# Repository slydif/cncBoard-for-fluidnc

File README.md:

KiCad PCB for fluidnc CNC router.
- Opto-coupled inputs with hysterese (schmitt triggers)
- 16 extra outputs with i2s driven shiftregisters.
- 2 relais can be used.
- 5 axes can be used.
- Buck-converter can be attached
- SD-card support.
- Tested and working.

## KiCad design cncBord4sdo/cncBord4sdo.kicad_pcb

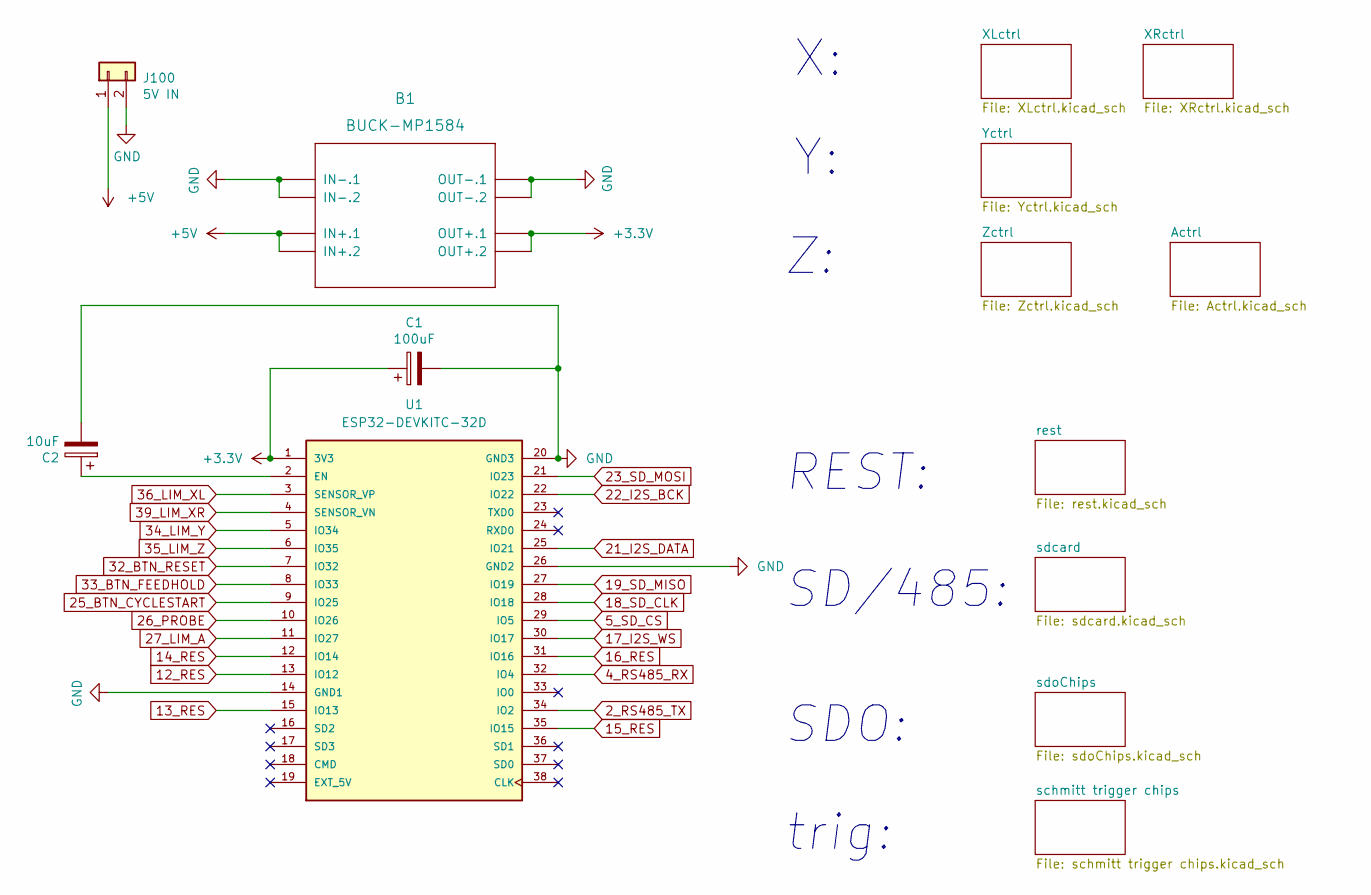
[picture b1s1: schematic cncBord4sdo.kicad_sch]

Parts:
B1: BUCK-MP1584; DC-DC-STEP-DOWN-MP1584
C1: 100uF; CP_Radial_D6.3mm_P2.50mm
C2: 10uF; CP_Radial_D6.3mm_P2.50mm
J100: 5V IN; PhoenixContact_MCV_1,5_2-G-5.08_1x02_P5.08mm_Vertical
U1: ESP32-DEVKITC-32D; MODULE_ESP32-DEVKITC-32D; PARTREV 4

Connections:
2_RS485_TX: U1.34 (IO2); also elsewhere on the board
4_RS485_RX: U1.32 (IO4); also elsewhere on the board
5_SD_CS: U1.29 (IO5); also elsewhere on the board
12_RES: U1.13 (IO12); also elsewhere on the board
13_RES: U1.15 (IO13); also elsewhere on the board
14_RES: U1.12 (IO14); also elsewhere on the board
15_RES: U1.35 (IO15); also elsewhere on the board
16_RES: U1.31 (IO16); also elsewhere on the board
17_I2S_WS: U1.30 (IO17); also elsewhere on the board
18_SD_CLK: U1.28 (IO18); also elsewhere on the board
19_SD_MISO: U1.27 (IO19); also elsewhere on the board
21_I2S_DATA: U1.25 (IO21); also elsewhere on the board
22_I2S_BCK: U1.22 (IO22); also elsewhere on the board
23_SD_MOSI: U1.21 (IO23); also elsewhere on the board
25_BTN_CYCLESTART: U1.9 (IO25); also elsewhere on the board
26_PROBE: U1.10 (IO26); also elsewhere on the board
27_LIM_A: U1.11 (IO27); also elsewhere on the board
32_BTN_RESET: U1.7 (IO32); also elsewhere on the board
33_BTN_FEEDHOLD: U1.8 (IO33); also elsewhere on the board
34_LIM_Y: U1.5 (IO34); also elsewhere on the board
35_LIM_Z: U1.6 (IO35); also elsewhere on the board
36_LIM_XL: U1.3 (SENSOR_VP); also elsewhere on the board
39_LIM_XR: U1.4 (SENSOR_VN); also elsewhere on the board
+3.3V: B1.OUT+.1, B1.OUT+.2, C1.1, U1.1 (3V3); also elsewhere on the board
+5V: B1.IN+.1, B1.IN+.2, J100.1; also elsewhere on the board
GND: B1.IN-.1, B1.IN-.2, B1.OUT-.1, B1.OUT-.2, C1.2, C2.2, J100.2, U1.14 (GND1), U1.20 (GND3), U1.26 (GND2); also elsewhere on the board
unnamed: C2.1, U1.2 (EN)

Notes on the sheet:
SDO:
trig:
SD/485:
REST:

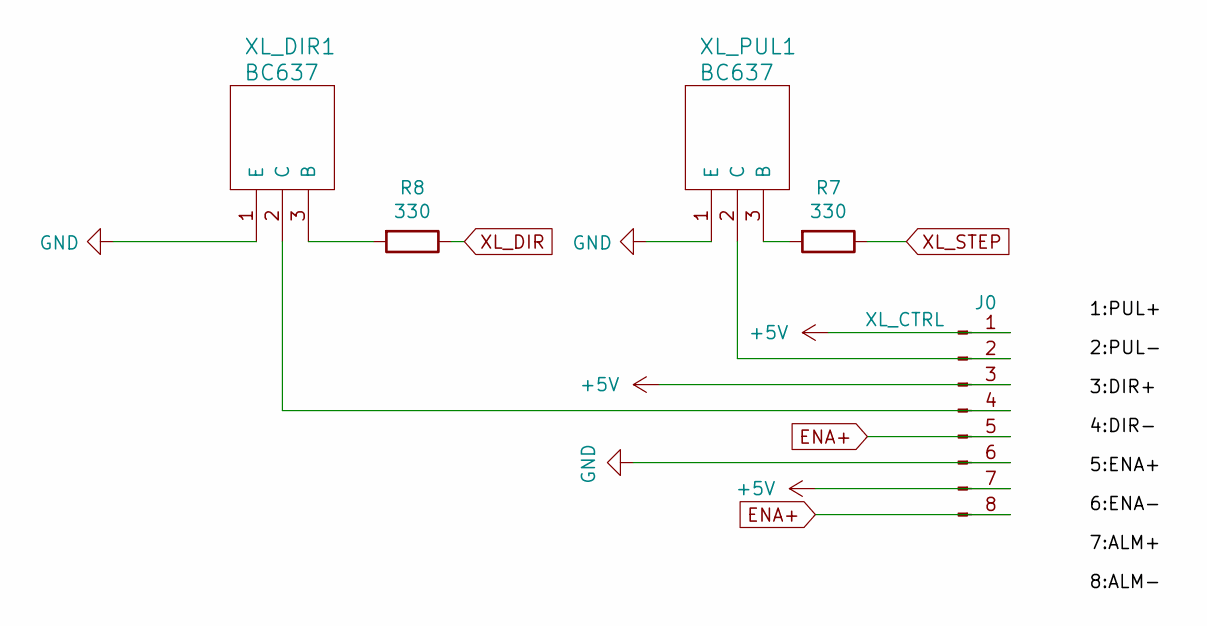
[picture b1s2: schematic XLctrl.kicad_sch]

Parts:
J0: XL_CTRL; JST_EH_B8B-EH-A_1x08_P2.50mm_Vertical
R7, R8: 330; R_1210_3225Metric_Pad1.30x2.65mm_HandSolder
XL_DIR1: BC637; TO-92_HandSolder
XL_PUL1: BC637; TO-92_HandSolder

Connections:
+5V: J0.1, J0.3, J0.7; also elsewhere on the board
ENA+: J0.5, J0.8; also elsewhere on the board
GND: J0.6, XL_DIR1.1 (E), XL_PUL1.1 (E); also elsewhere on the board
unnamed: J0.4, XL_DIR1.2 (C)
unnamed: R7.2, XL_PUL1.3 (B)
unnamed: R8.2, XL_DIR1.3 (B)
unnamed: J0.2, XL_PUL1.2 (C)
XL_DIR: R8.1; also elsewhere on the board
XL_STEP: R7.1; also elsewhere on the board

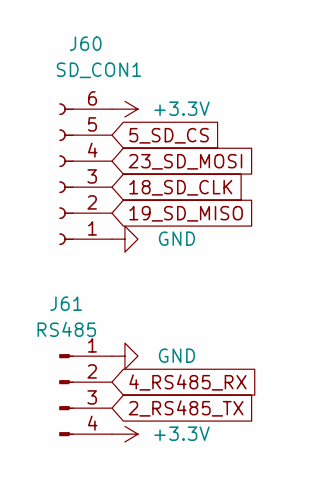
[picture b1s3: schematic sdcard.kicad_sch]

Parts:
J60: SD_CON1; PinHeader_1x06_P2.54mm_Vertical
J61: RS485; PinHeader_1x04_P2.54mm_Vertical

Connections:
2_RS485_TX: J61.3; also elsewhere on the board
4_RS485_RX: J61.2; also elsewhere on the board
5_SD_CS: J60.5; also elsewhere on the board
18_SD_CLK: J60.3; also elsewhere on the board
19_SD_MISO: J60.2; also elsewhere on the board
23_SD_MOSI: J60.4; also elsewhere on the board
+3.3V: J60.6, J61.4; also elsewhere on the board
GND: J60.1, J61.1; also elsewhere on the board

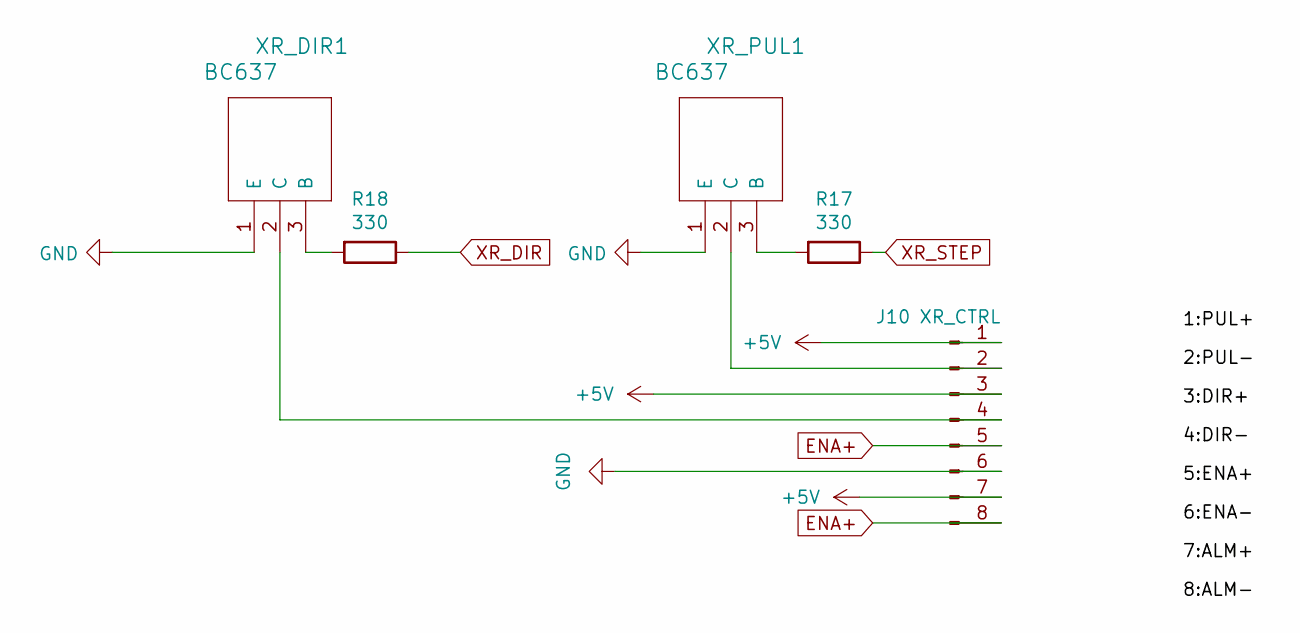
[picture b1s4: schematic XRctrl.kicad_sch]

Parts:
J10: XR_CTRL; JST_EH_B8B-EH-A_1x08_P2.50mm_Vertical
R17, R18: 330; R_1210_3225Metric_Pad1.30x2.65mm_HandSolder
XR_DIR1: BC637; TO-92_HandSolder
XR_PUL1: BC637; TO-92_HandSolder

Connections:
+5V: J10.1, J10.3, J10.7; also elsewhere on the board
ENA+: J10.5, J10.8; also elsewhere on the board
GND: J10.6, XR_DIR1.1 (E), XR_PUL1.1 (E); also elsewhere on the board
unnamed: J10.2, XR_PUL1.2 (C)
unnamed: J10.4, XR_DIR1.2 (C)
unnamed: R17.2, XR_PUL1.3 (B)
unnamed: R18.2, XR_DIR1.3 (B)
XR_DIR: R18.1; also elsewhere on the board
XR_STEP: R17.1; also elsewhere on the board

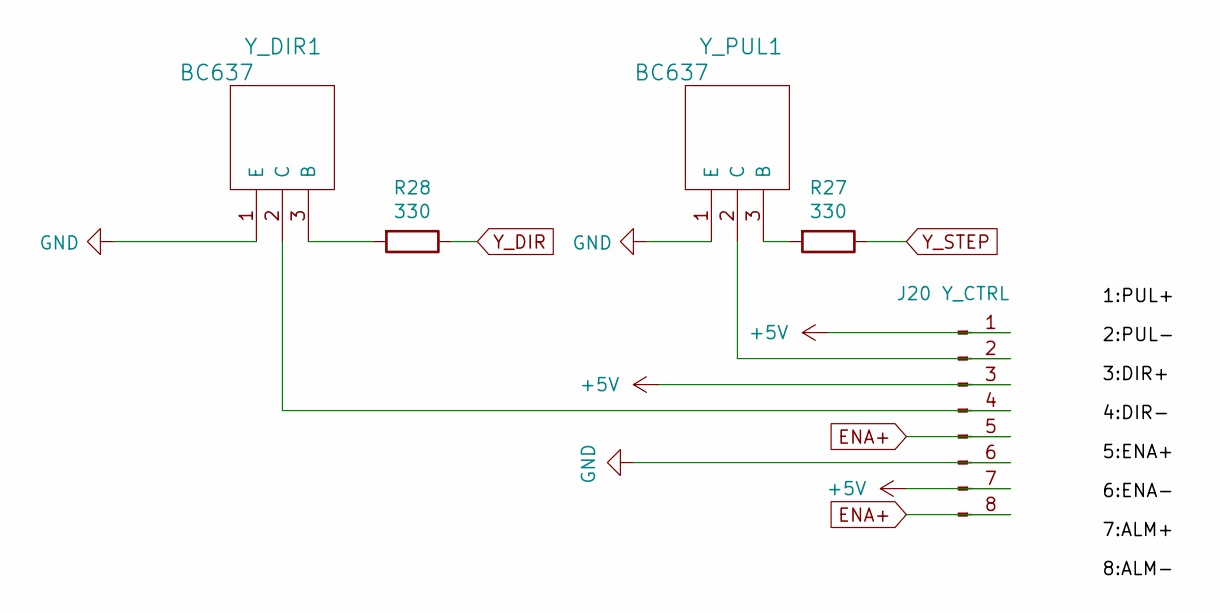
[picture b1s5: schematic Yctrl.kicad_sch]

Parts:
J20: Y_CTRL; JST_EH_B8B-EH-A_1x08_P2.50mm_Vertical
R27, R28: 330; R_1210_3225Metric_Pad1.30x2.65mm_HandSolder
Y_DIR1: BC637; TO-92_HandSolder
Y_PUL1: BC637; TO-92_HandSolder

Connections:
+5V: J20.1, J20.3, J20.7; also elsewhere on the board
ENA+: J20.5, J20.8; also elsewhere on the board
GND: J20.6, Y_DIR1.1 (E), Y_PUL1.1 (E); also elsewhere on the board
unnamed: R27.2, Y_PUL1.3 (B)
unnamed: R28.2, Y_DIR1.3 (B)
unnamed: J20.4, Y_DIR1.2 (C)
unnamed: J20.2, Y_PUL1.2 (C)
Y_DIR: R28.1; also elsewhere on the board
Y_STEP: R27.1; also elsewhere on the board

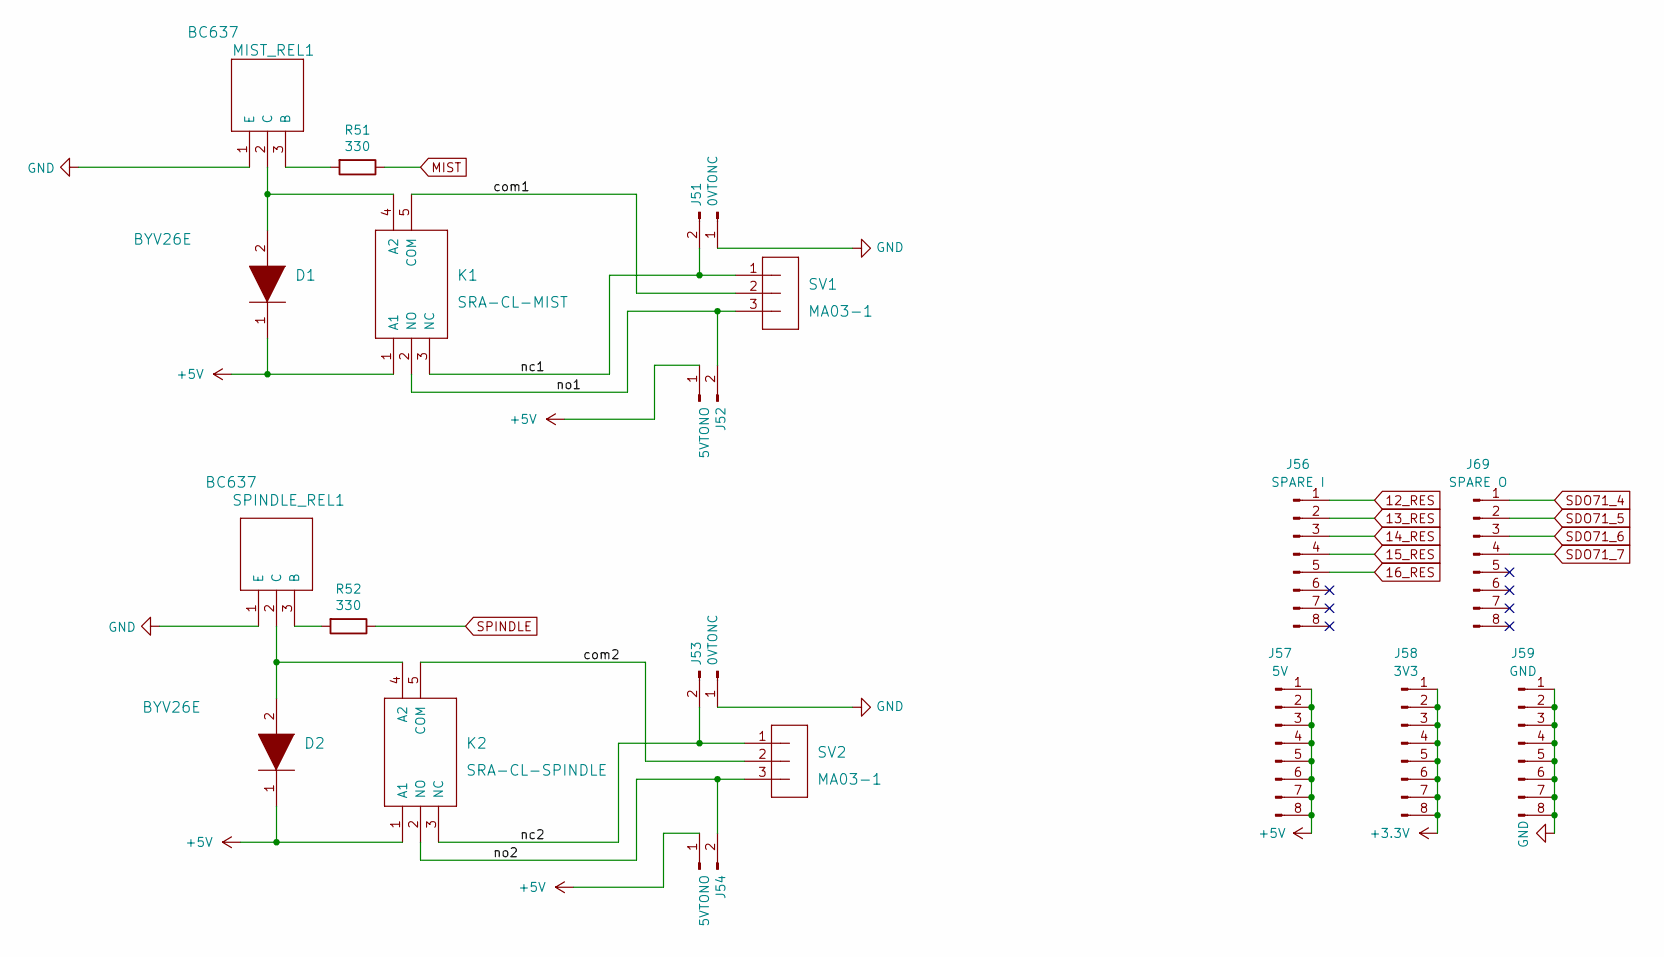
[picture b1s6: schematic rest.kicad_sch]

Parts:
D1, D2: BYV26E; D_A-405_P7.62mm_Horizontal
J51, J53: 0VTONC; PinHeader_1x02_P2.54mm_Vertical
J52, J54: 5VTONO; PinHeader_1x02_P2.54mm_Vertical
J56: SPARE I; PinHeader_1x08_P2.54mm_Vertical
J57: 5V; PinHeader_1x08_P2.54mm_Vertical
J58: 3V3; PinHeader_1x08_P2.54mm_Vertical
J59: GND; PinHeader_1x08_P2.54mm_Vertical
J69: SPARE O; PinHeader_1x08_P2.54mm_Vertical
K1: SRA-CL-MIST; SRA12VDCCL
K2: SRA-CL-SPINDLE; SRA12VDCCL
MIST_REL1: BC637; TO-92_HandSolder
R51, R52: 330; R_1210_3225Metric_Pad1.30x2.65mm_HandSolder
SPINDLE_REL1: BC637; TO-92_HandSolder
SV1, SV2: MA03-1; PhoenixContact_MCV_1,5_3-G-5.08_1x03_P5.08mm_Vertical

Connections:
12_RES: J56.1; also elsewhere on the board
13_RES: J56.2; also elsewhere on the board
14_RES: J56.3; also elsewhere on the board
15_RES: J56.4; also elsewhere on the board
16_RES: J56.5; also elsewhere on the board
+3.3V: J58.1, J58.2, J58.3, J58.4, J58.5, J58.6, J58.7, J58.8; also elsewhere on the board
+5V: D1.1 (K), D2.1 (K), J52.1, J54.1, J57.1, J57.2, J57.3, J57.4, J57.5, J57.6, J57.7, J57.8, K1.1 (A1), K2.1 (A1); also elsewhere on the board
/rest/com1: K1.5 (COM), SV1.2
/rest/com2: K2.5 (COM), SV2.2
/rest/nc1: J51.2, K1.3 (NC), SV1.1
/rest/nc2: J53.2, K2.3 (NC), SV2.1
/rest/no1: J52.2, K1.2 (NO), SV1.3
/rest/no2: J54.2, K2.2 (NO), SV2.3
GND: J51.1, J53.1, J59.1, J59.2, J59.3, J59.4, J59.5, J59.6, J59.7, J59.8, MIST_REL1.1 (E), SPINDLE_REL1.1 (E); also elsewhere on the board
MIST: R51.1; also elsewhere on the board
unnamed: D1.2 (A), K1.4 (A2), MIST_REL1.2 (C)
unnamed: D2.2 (A), K2.4 (A2), SPINDLE_REL1.2 (C)
unnamed: MIST_REL1.3 (B), R51.2
unnamed: R52.2, SPINDLE_REL1.3 (B)
SDO71_4: J69.1; also elsewhere on the board
SDO71_5: J69.2; also elsewhere on the board
SDO71_6: J69.3; also elsewhere on the board
SDO71_7: J69.4; also elsewhere on the board
SPINDLE: R52.1; also elsewhere on the board

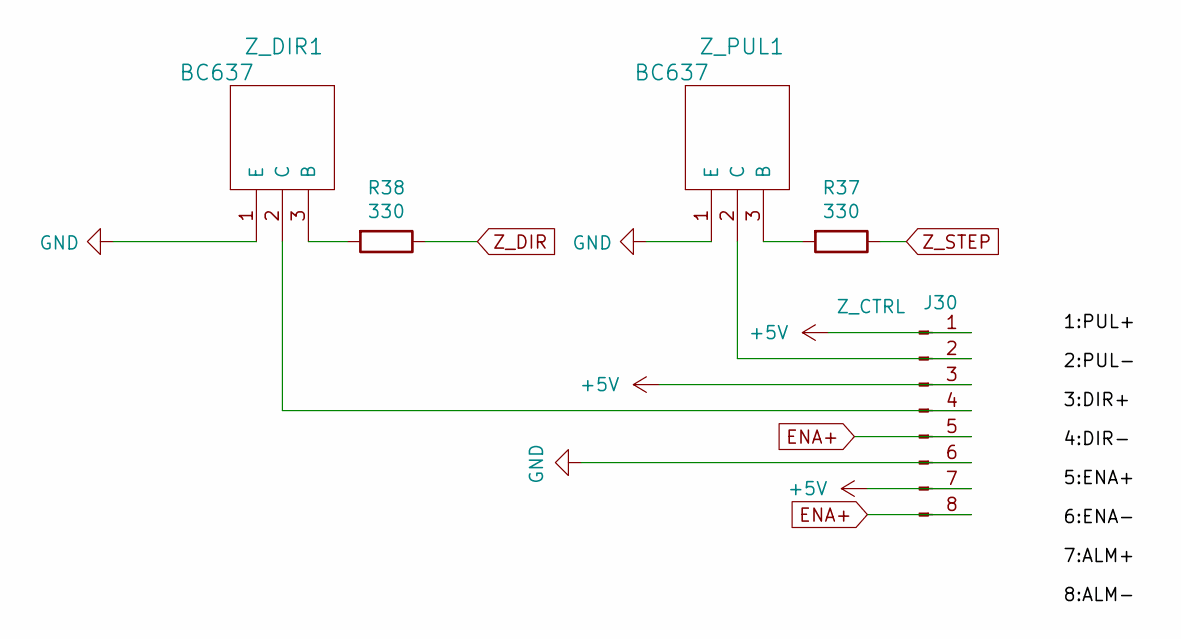
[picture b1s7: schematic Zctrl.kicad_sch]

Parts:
J30: Z_CTRL; JST_EH_B8B-EH-A_1x08_P2.50mm_Vertical
R37, R38: 330; R_1210_3225Metric_Pad1.30x2.65mm_HandSolder
Z_DIR1: BC637; TO-92_HandSolder
Z_PUL1: BC637; TO-92_HandSolder

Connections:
+5V: J30.1, J30.3, J30.7; also elsewhere on the board
ENA+: J30.5, J30.8; also elsewhere on the board
GND: J30.6, Z_DIR1.1 (E), Z_PUL1.1 (E); also elsewhere on the board
unnamed: R37.2, Z_PUL1.3 (B)
unnamed: R38.2, Z_DIR1.3 (B)
unnamed: J30.4, Z_DIR1.2 (C)
unnamed: J30.2, Z_PUL1.2 (C)
Z_DIR: R38.1; also elsewhere on the board
Z_STEP: R37.1; also elsewhere on the board

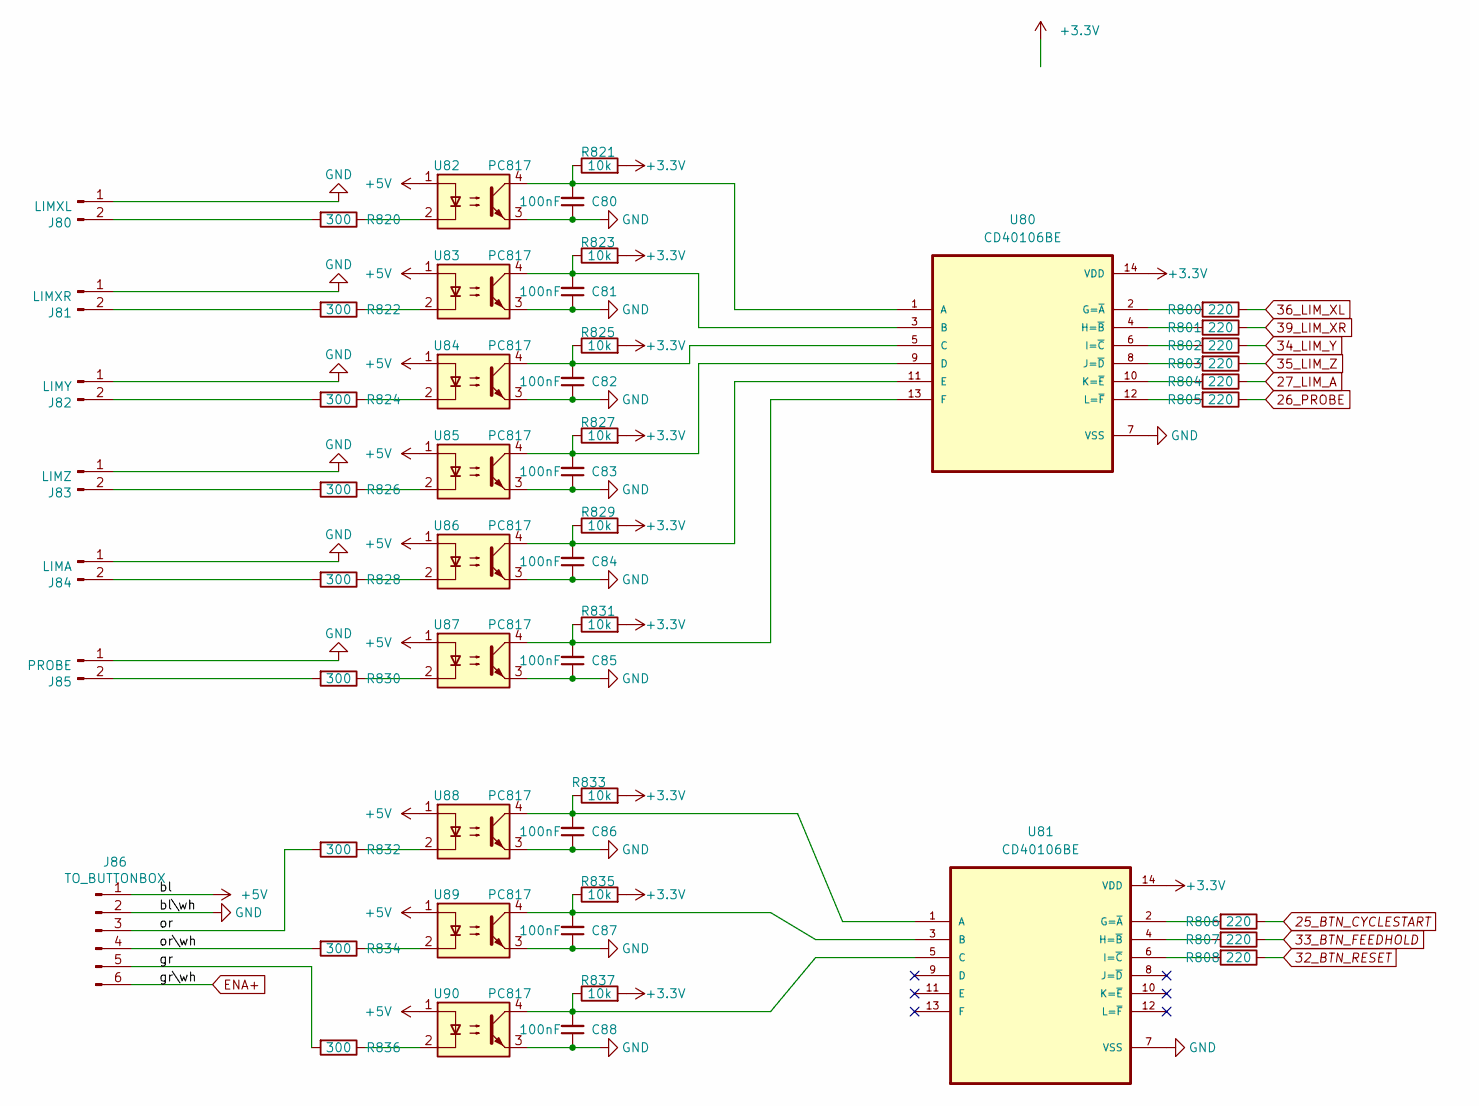
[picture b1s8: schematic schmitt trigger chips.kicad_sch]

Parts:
C80, C81, C82, C83, C84, C85, C86, C87, C88: 100nF; C_Disc_D5.0mm_W2.5mm_P2.50mm
J80: LIMXL; JST_EH_B2B-EH-A_1x02_P2.50mm_Vertical
J81: LIMXR; JST_EH_B2B-EH-A_1x02_P2.50mm_Vertical
J82: LIMY; JST_EH_B2B-EH-A_1x02_P2.50mm_Vertical
J83: LIMZ; JST_EH_B2B-EH-A_1x02_P2.50mm_Vertical
J84: LIMA; JST_EH_B2B-EH-A_1x02_P2.50mm_Vertical
J85: PROBE; JST_EH_B2B-EH-A_1x02_P2.50mm_Vertical
J86: TO_BUTTONBOX; JST_EH_B6B-EH-A_1x06_P2.50mm_Vertical
R800, R801, R802, R803, R804, R805, R806, R807, R808: 220; R_1210_3225Metric_Pad1.30x2.65mm_HandSolder
R820, R822, R824, R826, R828, R830, R832, R834, R836: 300; R_1210_3225Metric_Pad1.30x2.65mm_HandSolder
R821, R823, R825, R827, R829, R831, R833, R835, R837: 10k; R_1210_3225Metric_Pad1.30x2.65mm_HandSolder
U80, U81: CD40106BE; DIP794W45P254L1969H508Q14
U82, U83, U84, U85, U86, U87, U88, U89, U90: PC817; DIP-4_W7.62mm

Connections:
25_BTN_CYCLESTART: R806.1; also elsewhere on the board
26_PROBE: R805.1; also elsewhere on the board
27_LIM_A: R804.1; also elsewhere on the board
32_BTN_RESET: R808.1; also elsewhere on the board
33_BTN_FEEDHOLD: R807.1; also elsewhere on the board
34_LIM_Y: R802.1; also elsewhere on the board
35_LIM_Z: R803.1; also elsewhere on the board
36_LIM_XL: R800.1; also elsewhere on the board
39_LIM_XR: R801.1; also elsewhere on the board
+3.3V: R821.2, R823.2, R825.2, R827.2, R829.2, R831.2, R833.2, R835.2, R837.2, U80.14 (VDD), U81.14 (VDD); also elsewhere on the board
+5V: J86.1, U82.1, U83.1, U84.1, U85.1, U86.1, U87.1, U88.1, U89.1, U90.1; also elsewhere on the board
/schmitt trigger chips/gr: J86.5, R836.2
/schmitt trigger chips/or: J86.3, R832.2
/schmitt trigger chips/or\wh: J86.4, R834.2
ENA+: J86.6; also elsewhere on the board
GND: C80.1, C81.1, C82.1, C83.1, C84.1, C85.1, C86.1, C87.1, C88.1, J80.1, J81.1, J82.1, J83.1, J84.1, J85.1, J86.2, U80.7 (VSS), U81.7 (VSS), U82.3, U83.3, U84.3, U85.3, U86.3, U87.3, U88.3, U89.3, U90.3; also elsewhere on the board
unnamed: C80.2, R821.1, U80.1 (A), U82.4
unnamed: C81.2, R823.1, U80.3 (B), U83.4
unnamed: C82.2, R825.1, U80.5 (C), U84.4
unnamed: C83.2, R827.1, U80.9 (D), U85.4
unnamed: C84.2, R829.1, U80.11 (E), U86.4
unnamed: C85.2, R831.1, U80.13 (F), U87.4
unnamed: C86.2, R833.1, U81.1 (A), U88.4
unnamed: C87.2, R835.1, U81.3 (B), U89.4
unnamed: C88.2, R837.1, U81.5 (C), U90.4
unnamed: J80.2, R820.2
unnamed: J81.2, R822.2
unnamed: J82.2, R824.2
unnamed: J83.2, R826.2
unnamed: J84.2, R828.2
unnamed: J85.2, R830.2
unnamed: R800.2, U80.2 (G=~A)
unnamed: R801.2, U80.4 (H=~B)
unnamed: R802.2, U80.6 (I=~C)
unnamed: R803.2, U80.8 (J=~D)
unnamed: R804.2, U80.10 (K=~E)
unnamed: R805.2, U80.12 (L=~F)
unnamed: R806.2, U81.2 (G=~A)
unnamed: R807.2, U81.4 (H=~B)
unnamed: R808.2, U81.6 (I=~C)
unnamed: R820.1, U82.2
unnamed: R822.1, U83.2
unnamed: R824.1, U84.2
unnamed: R826.1, U85.2
unnamed: R828.1, U86.2
unnamed: R830.1, U87.2
unnamed: R832.1, U88.2
unnamed: R834.1, U89.2
unnamed: R836.1, U90.2

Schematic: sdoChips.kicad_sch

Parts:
C70, C71: 100nF; C_Disc_D5.0mm_W2.5mm_P2.50mm
R70: 10k; R_1210_3225Metric_Pad1.30x2.65mm_HandSolder
U70, U71: 74AHC595; DIP-16_W7.62mm_Socket

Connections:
17_I2S_WS: U70.12 (RCLK), U71.12 (RCLK); also elsewhere on the board
21_I2S_DATA: U70.14 (SER); also elsewhere on the board
22_I2S_BCK: R70.2, U70.11 (SRCLK), U71.11 (SRCLK); also elsewhere on the board
+3.3V: C70.1, C71.1, U70.10 (~SRCLR), U70.16 (VCC), U71.10 (~SRCLR), U71.16 (VCC); also elsewhere on the board
A_DIR: U71.15 (QA); also elsewhere on the board
A_STEP: U71.1 (QB); also elsewhere on the board
GND: C70.2, C71.2, R70.1, U70.8 (GND), U70.13 (~OE), U71.8 (GND), U71.13 (~OE); also elsewhere on the board
MIST: U71.3 (QD); also elsewhere on the board
unnamed: U70.9 (QH'), U71.14 (SER)
SDO71_4: U71.4 (QE); also elsewhere on the board
SDO71_5: U71.5 (QF); also elsewhere on the board
SDO71_6: U71.6 (QG); also elsewhere on the board
SDO71_7: U71.7 (QH); also elsewhere on the board
SPINDLE: U71.2 (QC); also elsewhere on the board
XL_DIR: U70.15 (QA); also elsewhere on the board
XL_STEP: U70.1 (QB); also elsewhere on the board
XR_DIR: U70.2 (QC); also elsewhere on the board
XR_STEP: U70.3 (QD); also elsewhere on the board
Y_DIR: U70.4 (QE); also elsewhere on the board
Y_STEP: U70.5 (QF); also elsewhere on the board
Z_DIR: U70.6 (QG); also elsewhere on the board
Z_STEP: U70.7 (QH); also elsewhere on the board

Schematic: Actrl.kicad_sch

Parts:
A_DIR1: BC637; TO-92_HandSolder
A_PUL1: BC637; TO-92_HandSolder
J40: A_CTRL; JST_EH_B8B-EH-A_1x08_P2.50mm_Vertical
R47, R48: 330; R_1210_3225Metric_Pad1.30x2.65mm_HandSolder

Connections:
+5V: J40.1, J40.3, J40.7; also elsewhere on the board
A_DIR: R48.1; also elsewhere on the board
A_STEP: R47.1; also elsewhere on the board
ENA+: J40.5, J40.8; also elsewhere on the board
GND: A_DIR1.1 (E), A_PUL1.1 (E), J40.6; also elsewhere on the board
unnamed: A_DIR1.2 (C), J40.4
unnamed: A_DIR1.3 (B), R48.2
unnamed: A_PUL1.2 (C), J40.2
unnamed: A_PUL1.3 (B), R47.2

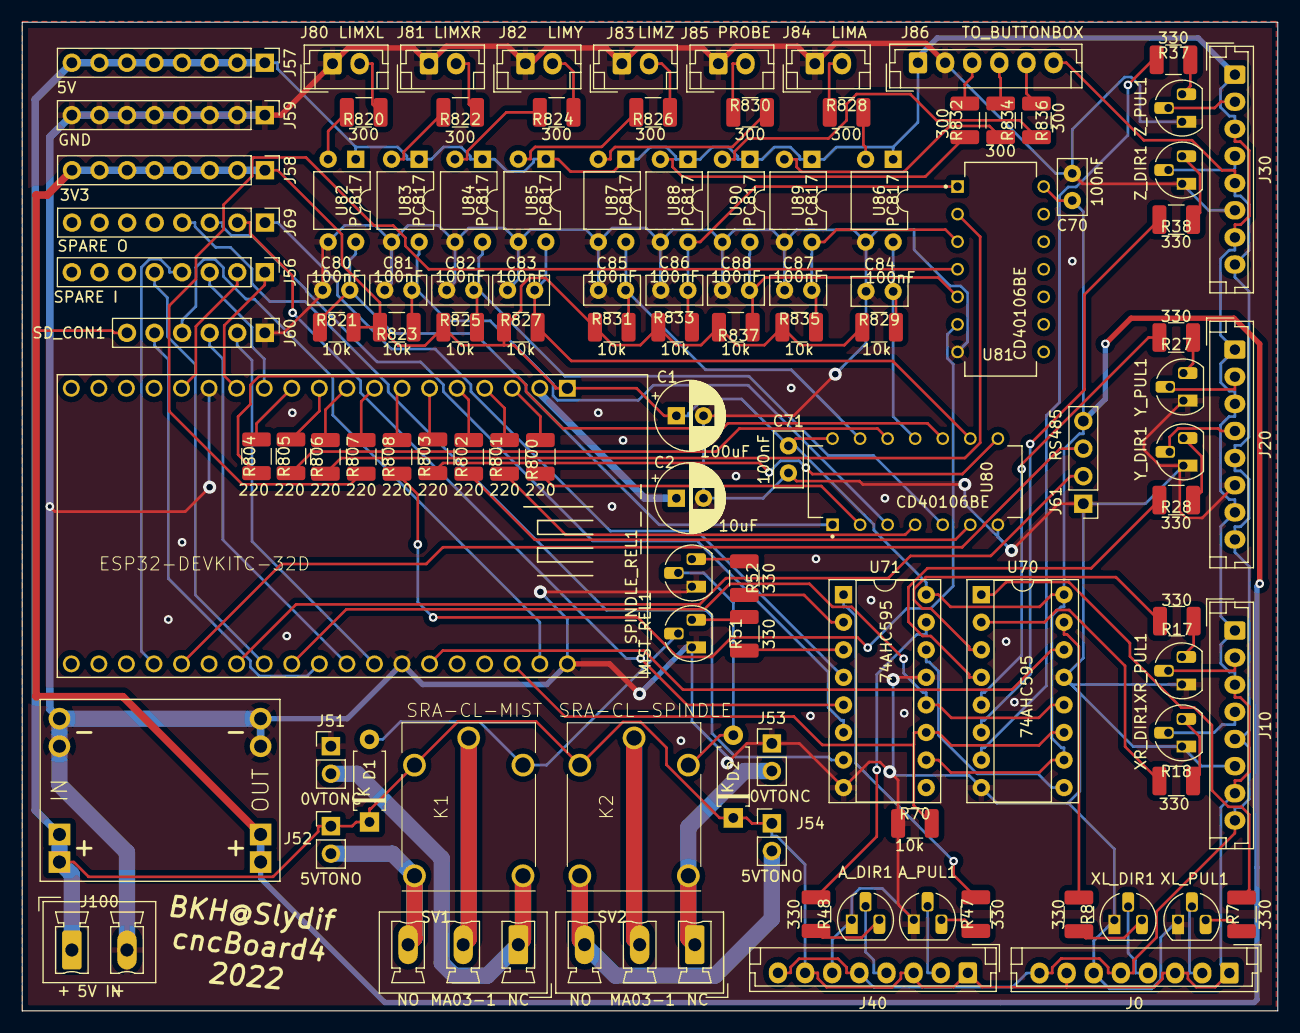
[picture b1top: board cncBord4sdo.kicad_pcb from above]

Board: 2 copper layers, 115.7 x 91.1 mm, 110 parts (0 on the bottom side), 111 nets.

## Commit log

2023-04-05 slydif board
2023-04-19 added readme
